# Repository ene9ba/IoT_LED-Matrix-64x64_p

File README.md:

# IoT_LED-Matrix-64x64_p
LED-Matrix Display driven by Raspi PICOW  Comchain: openHAB - mqtt - wifi - display develoed with platformio
**IoT RGB-Matrixdisplay to visualize temperatures from air ant HOT Tub via WiFi over MQTT to openHAB**

# Goal of this project
To use a 64x64 RGB matrix display for visualisation of temperature, time and systemstate of my HotTub (whrilpool).
The picture should be absolute flickerree.

The project consits of three parts:

## Part 1: 
Hardwaredesign controller RP 2040 PICO W and powershifting 3.3 V to 5 V 

## Part 2: 
Softwaredevelopment matrix control, connection to Wifi, connection to mqtt 

## Part 3: 3D Case design

## Info:
The LED-Panel is integrated in a self designed case with integrated power supply. Communication to SMART-Home runs via WiFi and MQTT to opnHAB.
The contoller I'm using is Raspberry Pi PICO RP2040 because it meets the requriements for WiFi and control the LED-panel **flickerfree** using the realtine state-machine on the chip.

The pcb will be pluged directly to the pins on the panel, there is no need for additional cabling.

Software ist developed with PlatformIO IDE.

I'm using displaytype RGB_LEF Joy-It. Most pinouts from other manaufactorers are the same, but have a look to the pcb pinout to be shure pining fits.

### Designfiles for the Case you can find on [thingeverese]() or [printables]().

### Credits and Acknowledgments
This project builds upon the work of the following contributors:

**:** For providing the initial groundwork and hardware interfacing for driving HUB75 LED Matrix panels with Raspberry Pi Pico's PIO

**Bodmer/Adafruit-GFX-Library:** For the core graphics library, enabling compatibility with Adafruit's GFX library and enhancing the display manipulation capabilities of the project.

**:** For adapt the software to run on pico w without FREERTOS (works now with Arduino WifFi libraries)

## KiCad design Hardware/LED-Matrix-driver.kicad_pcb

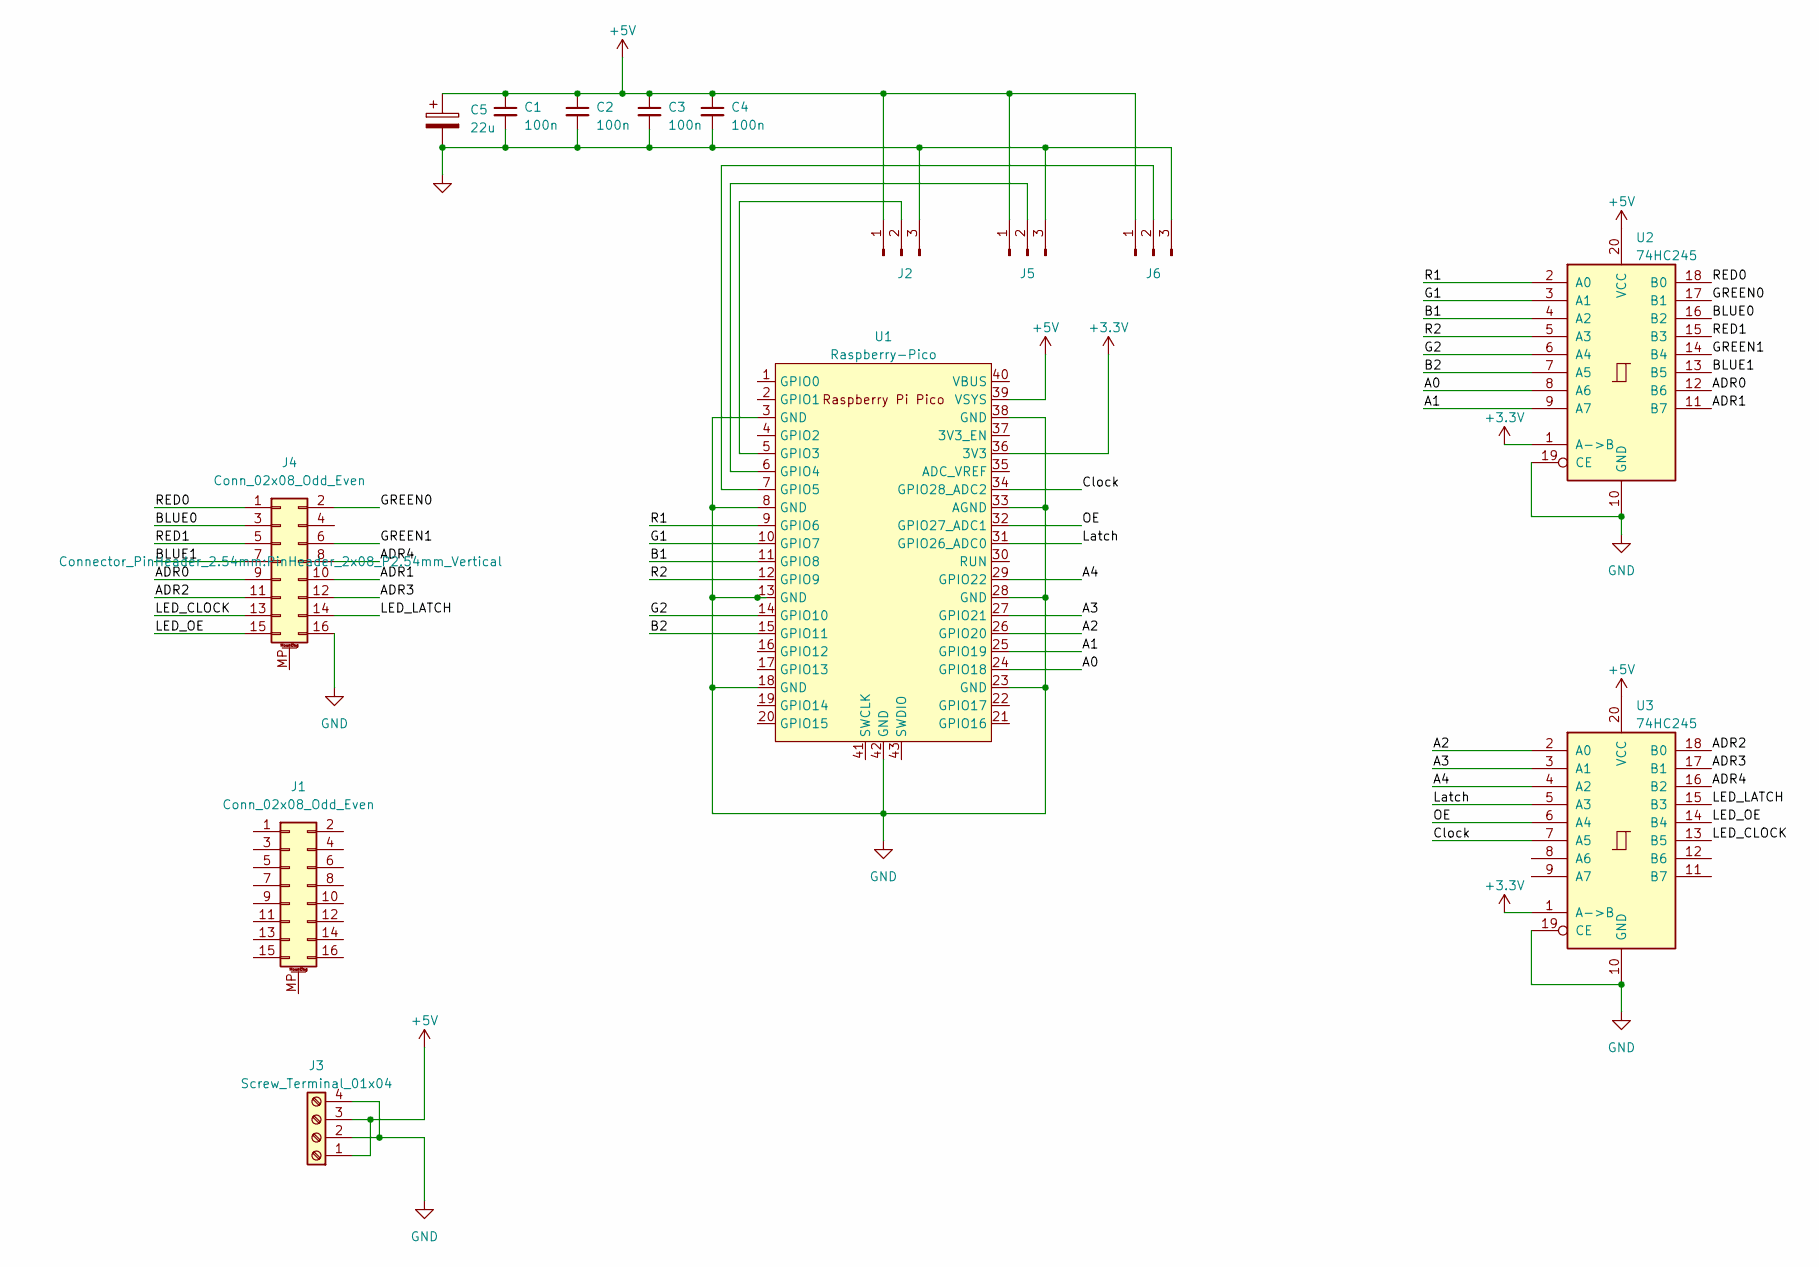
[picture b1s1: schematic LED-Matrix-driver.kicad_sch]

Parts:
C1, C2, C3, C4: 100n; C_Disc_D5.0mm_W2.5mm_P5.00mm
C5: 22u; CP_Radial_D8.0mm_P5.00mm
J1, J4: Conn_02x08_Odd_Even; PinHeader_2x08_P2.54mm_Vertical
J2, J5, J6: Conn_01x03_Pin; JST_XH_B3B-XH-A_1x03_P2.50mm_Vertical
J3: Screw_Terminal_01x04; PhoenixContact_GMSTBA_2,5_4-G-7,62_1x04_P7.62mm_Horizontal
U1: Raspberry-Pico; MODULE_SC0918
U2, U3: 74HC245; SOIC127P1032X265-20N

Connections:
+3.3V: U1.36 (3V3), U2.1 (A->B), U3.1 (A->B)
+5V: C1.1, C2.1, C3.1, C4.1, C5.1, J2.1, J3.1, J3.3, J5.1, J6.1, U1.39 (VSYS), U2.20 (VCC), U3.20 (VCC)
/A0: U1.24 (GPIO18), U2.8 (A6)
/A1: U1.25 (GPIO19), U2.9 (A7)
/A2: U1.26 (GPIO20), U3.2 (A0)
/A3: U1.27 (GPIO21), U3.3 (A1)
/A4: U1.29 (GPIO22), U3.4 (A2)
/ADR0: J4.9, U2.12 (B6)
/ADR1: J4.10, U2.11 (B7)
/ADR2: J4.11, U3.18 (B0)
/ADR3: J4.12, U3.17 (B1)
/ADR4: J4.8, U3.16 (B2)
/B1: U1.11 (GPIO8), U2.4 (A2)
/B2: U1.15 (GPIO11), U2.7 (A5)
/BLUE0: J4.3, U2.16 (B2)
/BLUE1: J4.7, U2.13 (B5)
/Clock: U1.34 (GPIO28_ADC2), U3.7 (A5)
/G1: U1.10 (GPIO7), U2.3 (A1)
/G2: U1.14 (GPIO10), U2.6 (A4)
/GREEN0: J4.2, U2.17 (B1)
/GREEN1: J4.6, U2.14 (B4)
/LED_CLOCK: J4.13, U3.13 (B5)
/LED_LATCH: J4.14, U3.15 (B3)
/LED_OE: J4.15, U3.14 (B4)
/Latch: U1.31 (GPIO26_ADC0), U3.5 (A3)
/OE: U1.32 (GPIO27_ADC1), U3.6 (A4)
/R1: U1.9 (GPIO6), U2.2 (A0)
/R2: U1.12 (GPIO9), U2.5 (A3)
/RED0: J4.1, U2.18 (B0)
/RED1: J4.5, U2.15 (B3)
GND: C1.2, C2.2, C3.2, C4.2, C5.2, J2.3, J3.2, J3.4, J4.16, J5.3, J6.3, U1.3 (GND), U1.8 (GND), U1.13 (GND), U1.18 (GND), U1.23 (GND), U1.28 (GND), U1.33 (AGND), U1.38 (GND), U1.42 (GND), U2.10 (GND), U2.19 (CE), U3.10 (GND), U3.19 (CE)
unnamed: J2.2, U1.5 (GPIO3)
unnamed: J5.2, U1.6 (GPIO4)
unnamed: J6.2, U1.7 (GPIO5)

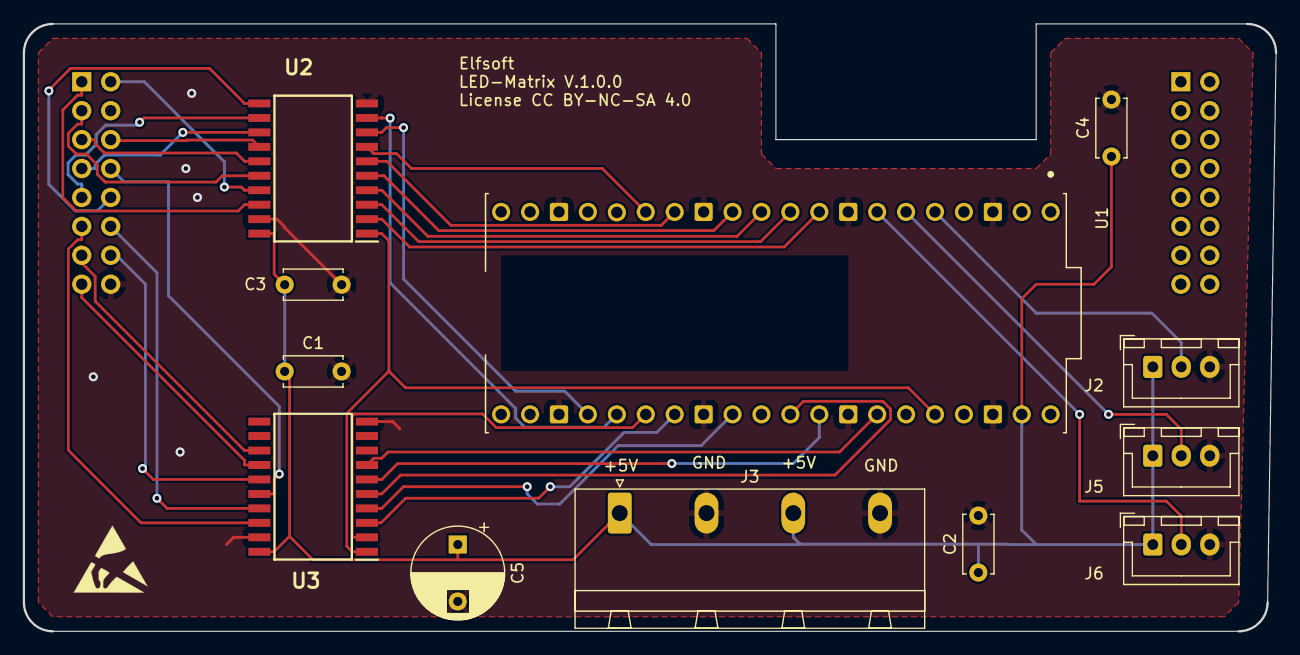
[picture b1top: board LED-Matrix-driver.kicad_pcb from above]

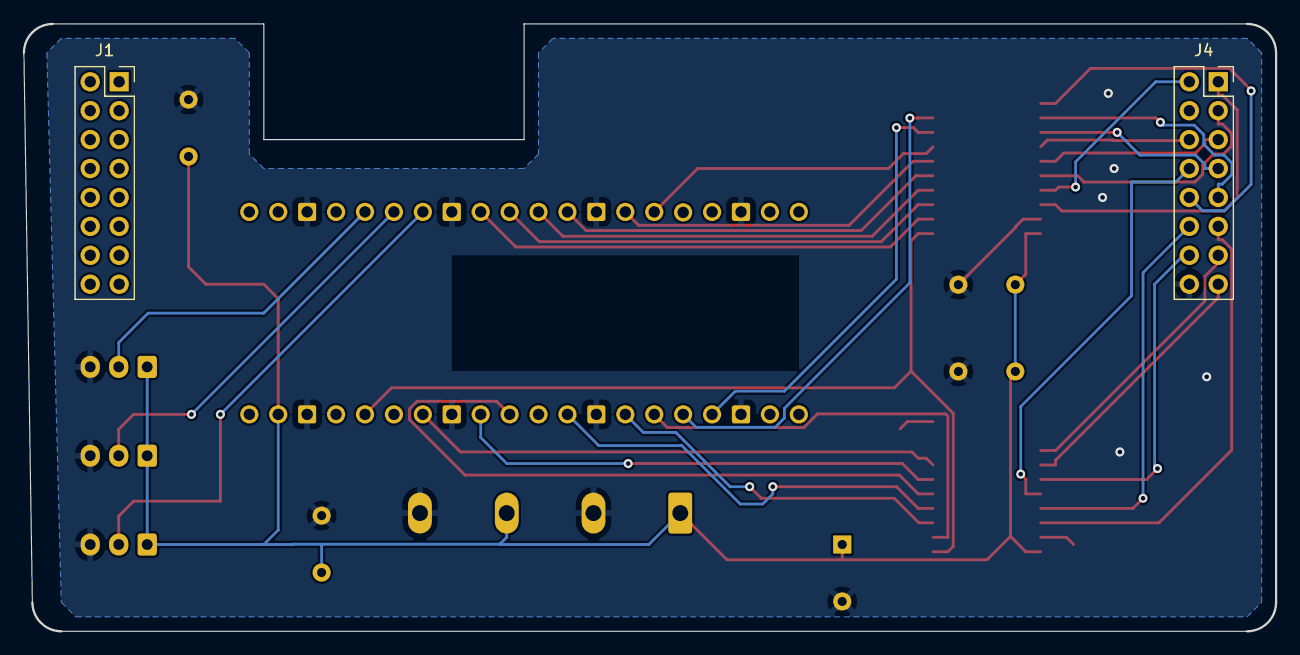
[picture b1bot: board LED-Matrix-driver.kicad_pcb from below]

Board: 2 copper layers, 110.0 x 53.3 mm, 15 parts (2 on the bottom side), 34 nets.

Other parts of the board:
LOGO2: ESD-Logo_6.6x6mm_SilkScreen

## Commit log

2024-04-16 initial
2024-04-16 added doc

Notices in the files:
Hardware/LED-Matrix-driver.kicad_pcb:
License CC BY-NC-SA 4.0
